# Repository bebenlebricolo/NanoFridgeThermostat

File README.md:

# NanoFridgeThermostat
Off-the-shelf fridge thermostat using an ArduinoNano to replace a broken fridge thermomechanical thermostat.

This project was born with the sole purpose of repairing a dying fridge whose thermostat was completely dead.
The idea is first to provide a very basic cooling support, with a simple on/off cycle that can be programmed using on seconds and off seconds.

The project also features a "bypass" switch that allows to manually trigger the fridge cooling process (useful for a fridge that first needs to be cooled down quite a lot before entering a "steady" on/off cycle ).

Polarity of said switch is meant for a circuit breaker switch type (because that's what I had around, so that explains why the logic is reversed.)
All components were components I had lying around :
* Arduino nano (clone, using the CH341 UART to USB bridge)
* Double relay board, with optoisolators as input.
* Wires and female header (single row, 2.54 mm pitch)
* Electrical tape to isolate components

# Future improvements
* Using a triac and triac driver as the main switching elements
    * Solid state is cool and removes the issue of relay contact points wearing down
* Adding a thermistor to measure temperature within the fridge and cycle towards a target temperature

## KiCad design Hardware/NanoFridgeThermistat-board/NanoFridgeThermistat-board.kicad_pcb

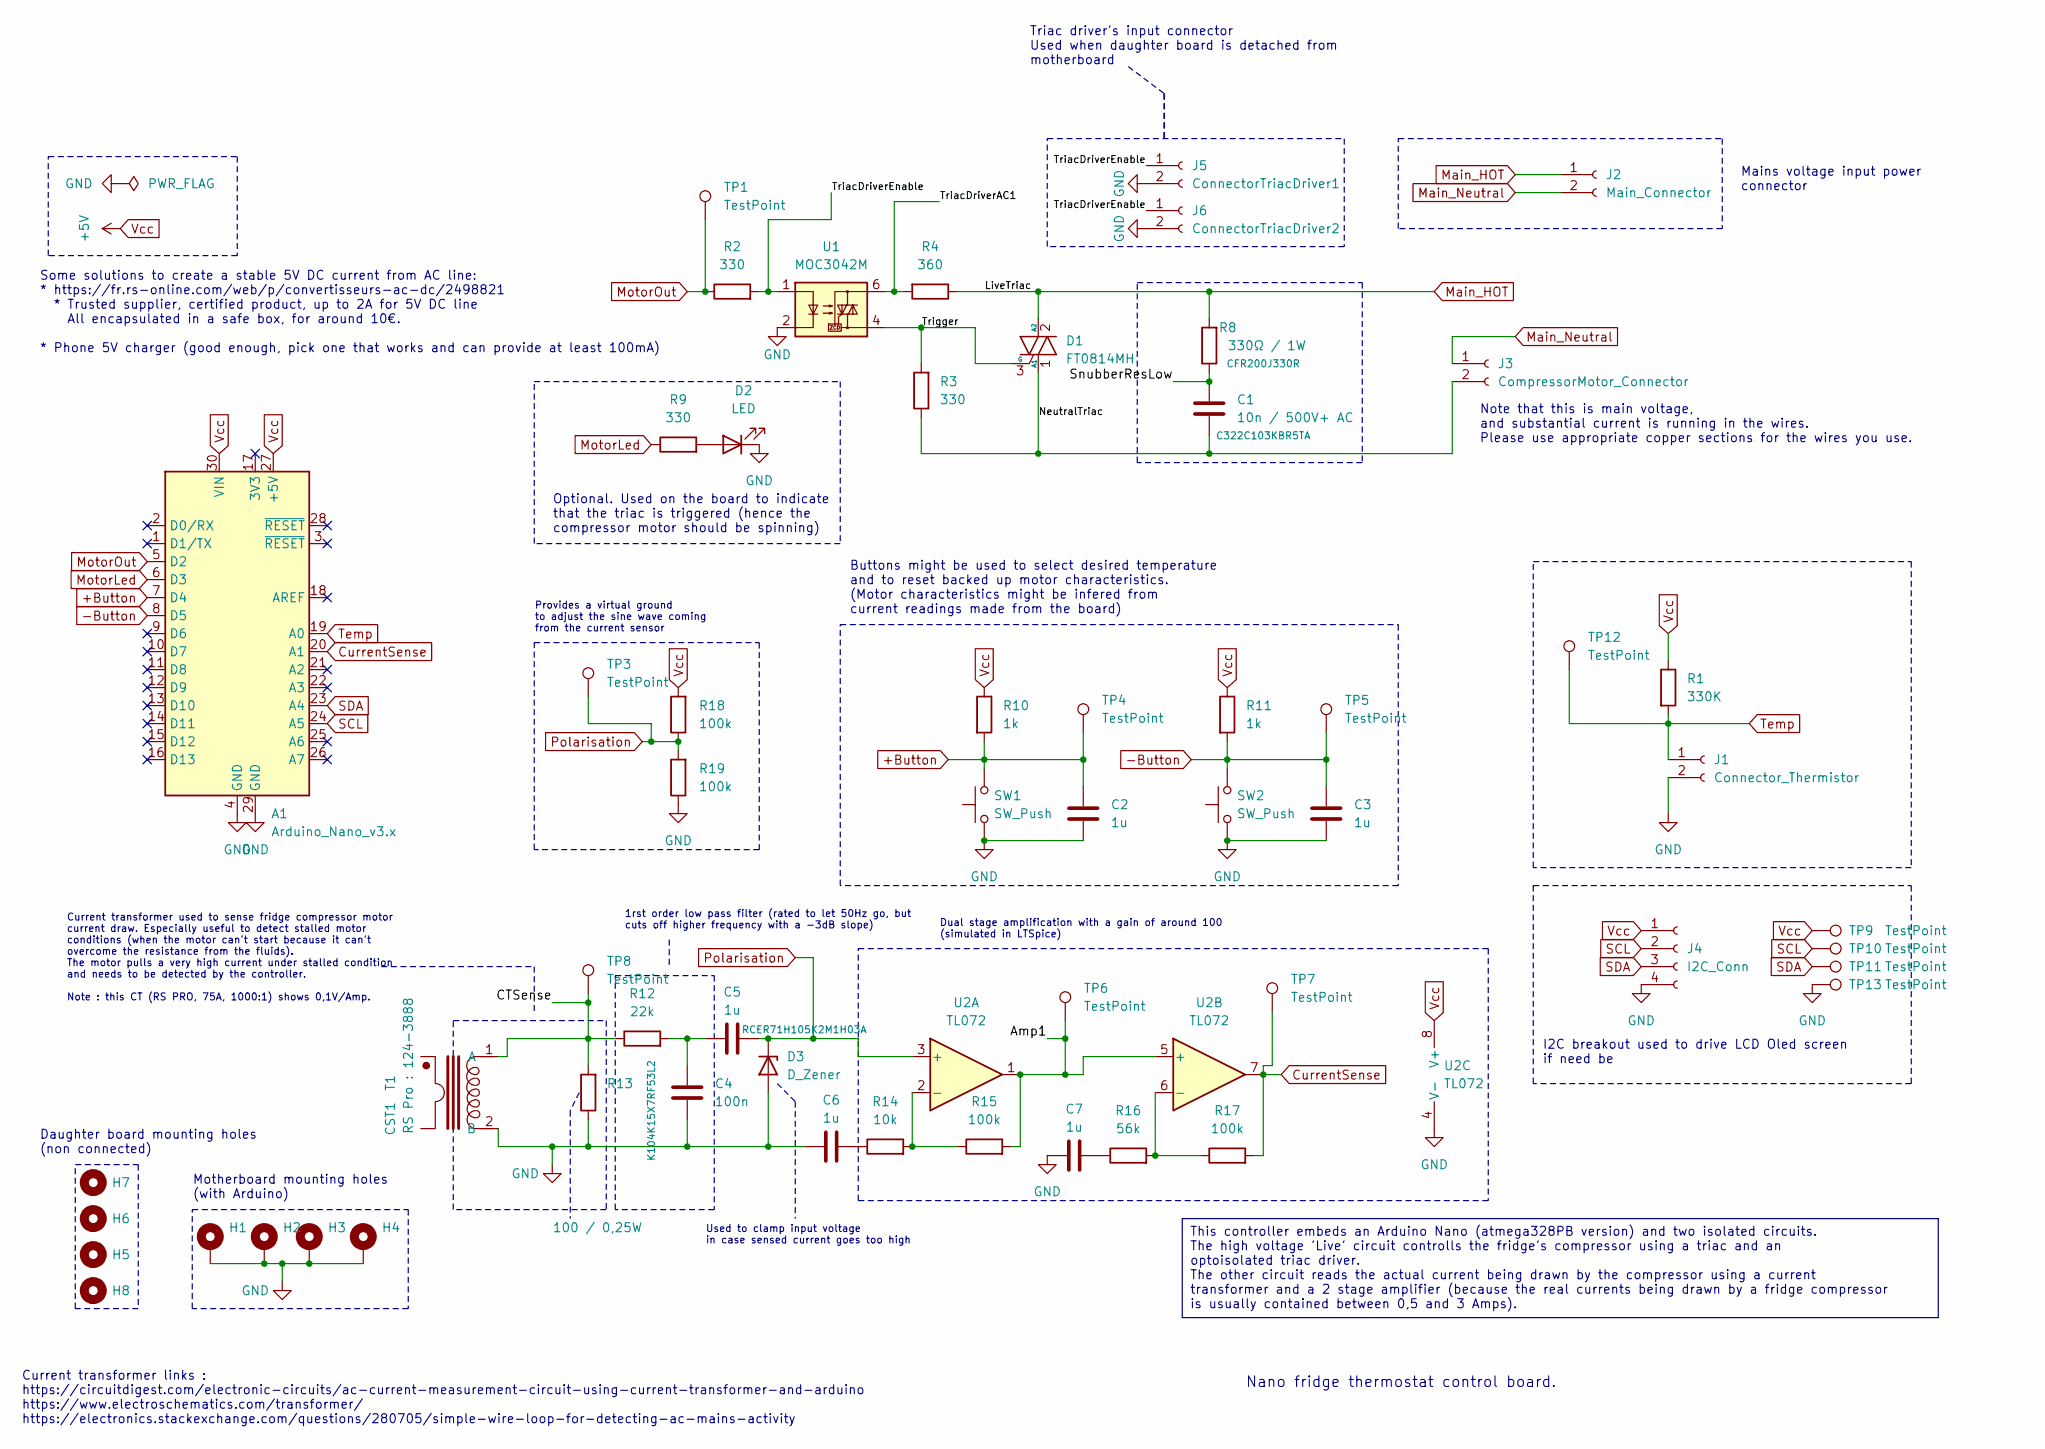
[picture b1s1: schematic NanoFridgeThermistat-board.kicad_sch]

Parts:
A1: Arduino_Nano_v3.x; Arduino_Nano
C1: 10n / 500V+ AC; C_Disc_D10.0mm_W2.5mm_P5.00mm
C2, C3, C5, C6, C7: 1u; C_Disc_D4.7mm_W2.5mm_P5.00mm
C4: 100n; C_Disc_D3.8mm_W2.6mm_P2.50mm
D1: FT0814MH; TO-220-3_Vertical
D2: LED; LED_D3.0mm
D3: D_Zener; D_DO-35_SOD27_P7.62mm_Horizontal
H1, H2, H3, H4: MountingHole_Pad; MountingHole_2.2mm_M2_DIN965_Pad
H5, H6, H7, H8: MountingHole; MountingHole_2.2mm_M2_ISO7380
J1: Connector_Thermistor; PinSocket_1x02_P2.54mm_Vertical
J2: Main_Connector; TE-282836-2-5.08mm
J3: CompressorMotor_Connector; TE-282836-2-5.08mm
J4: I2C_Conn; PinSocket_1x04_P2.54mm_Vertical
J5: ConnectorTriacDriver1; PinSocket_1x02_P2.54mm_Vertical
J6: ConnectorTriacDriver2; PinSocket_1x02_P2.54mm_Vertical
R1: 330K; R_Axial_DIN0207_L6.3mm_D2.5mm_P10.16mm_Horizontal
R2, R3, R9: 330; R_Axial_DIN0207_L6.3mm_D2.5mm_P10.16mm_Horizontal
R4: 360; R_Axial_DIN0207_L6.3mm_D2.5mm_P10.16mm_Horizontal
R8: 330Ω / 1W; R_Axial_DIN0614_L14.3mm_D5.7mm_P20.32mm_Horizontal
R10, R11: 1k; R_Axial_DIN0207_L6.3mm_D2.5mm_P10.16mm_Horizontal
R12: 22k; R_Axial_DIN0207_L6.3mm_D2.5mm_P10.16mm_Horizontal
R13: 100 / 0,25W; R_Axial_DIN0207_L6.3mm_D2.5mm_P10.16mm_Horizontal
R14: 10k; R_Axial_DIN0207_L6.3mm_D2.5mm_P10.16mm_Horizontal
R15, R17, R18, R19: 100k; R_Axial_DIN0207_L6.3mm_D2.5mm_P10.16mm_Horizontal
R16: 56k; R_Axial_DIN0207_L6.3mm_D2.5mm_P10.16mm_Horizontal
SW1, SW2: SW_Push; SW_PUSH_6mm
T1: CST1; CT-RSPRO-1243888
TP1, TP3, TP4, TP5, TP6, TP7, TP8, TP9, TP10, TP11, TP12, TP13: TestPoint; TestPoint_Pad_D1.0mm
U1: MOC3042M; DIP-6_W7.62mm
U2: TL072; DIP-8_W7.62mm

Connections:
+Button: A1.7 (D4), C2.1, R10.2, SW1.2, TP4.1
-Button: A1.8 (D5), C3.1, R11.2, SW2.2, TP5.1
/Amp1: R15.2, TP6.1, U2.1, U2.5 (+)
/CTSense: R12.1, R13.2, T1.1 (A), TP8.1
/NeutralTriac: C1.2, D1.1 (A1), J3.2, R3.1
/SnubberResLow: C1.1, R8.1
/TriacDriverAC1: R4.2, U1.6
/TriacDriverEnable: J5.1, J6.1, R2.2, U1.1
/Trigger: D1.3 (G), R3.2, U1.4
CurrentSense: A1.20 (A1), R17.2, TP7.1, U2.7
GND: A1.4 (GND), A1.29 (GND), C2.2, C3.2, C4.2, C6.1, C7.1, D2.1 (K), D3.2 (A), H1.1, H2.1, H3.1, H4.1, J1.2, J4.4, J5.2, J6.2, R13.1, R19.1, SW1.1, SW2.1, T1.2 (B), TP13.1, U1.2, U2.4 (V-)
Main_HOT: D1.2 (A2), J2.1, R4.1, R8.2
Main_Neutral: J2.2, J3.1
MotorLed: A1.6 (D3), R9.1
MotorOut: A1.5 (D2), R2.1, TP1.1
unnamed: C4.1, C5.1, R12.2
unnamed: C6.2, R14.1
unnamed: C7.2, R16.1
unnamed: D2.2 (A), R9.2
unnamed: R14.2, R15.1, U2.2 (-)
unnamed: R16.2, R17.1, U2.6 (-)
Polarisation: C5.2, D3.1 (K), R18.1, R19.2, TP3.1, U2.3 (+)
SCL: A1.24 (A5), J4.2, TP10.1
SDA: A1.23 (A4), J4.3, TP11.1
Temp: A1.19 (A0), J1.1, R1.2, TP12.1
Vcc: A1.27 (+5V), A1.30 (VIN), J4.1, R1.1, R10.1, R11.1, R18.2, TP9.1, U2.8 (V+)

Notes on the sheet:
This controller embeds an Arduino Nano (atmega328PB version) and two isolated circuits. The high voltage 'Live' circuit controlls the fridge's compressor using a triac and an optoisolated triac driver. The other circuit reads the actual current being drawn by the compressor using a current transfor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
Current transformer used to sense fridge compressor motor current draw. Especially useful to detect stalled motor conditions (when the motor can't start because it can't overcome the resistance from the fluids). The motor pulls a very high current under stalled condition and needs to be detected by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
Dual stage amplification with a gain of around 100 (simulated in LTSpice)
Triac driver's input connector Used when daughter board is detached from motherboard
Note that this is main voltage, and substantial current is running in the wires. Please use appropriate copper sections for the wires you use.
Provides a virtual ground to adjust the sine wave coming from the current sensor
Nano fridge thermostat control board.
1rst order low pass filter (rated to let 50Hz go, but cuts off higher frequency with a -3dB slope)
Daughter board mounting holes (non connected)
Optional. Used on the board to indicate that the triac is triggered (hence the compressor motor should be spinning)
Some solutions to create a stable 5V DC current from AC line: * https://fr.rs-online.com/web/p/convertisseurs-ac-dc/2498821 * Trusted supplier, certified product, up to 2A for 5V DC line All encapsulated in a safe box, for around 10€. * Phone 5V charger (good enough, pick one that works and can pro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
Buttons might be used to select desired temperature and to reset backed up motor characteristics. (Motor characteristics might be infered from current readings made from the board)
Motherboard mounting holes (with Arduino)
Mains voltage input power connector
I2C breakout used to drive LCD Oled screen if need be
Used to clamp input voltage in case sensed current goes too high
Current transformer links : https://circuitdigest.com/electronic-circuits/ac-current-measurement-circuit-using-current-transformer-and-arduino https://www.electroschematics.com/transformer/ https://electronics.stackexchange.com/questions/280705/simple-wire-loop-for-detecting-ac-mains-activity

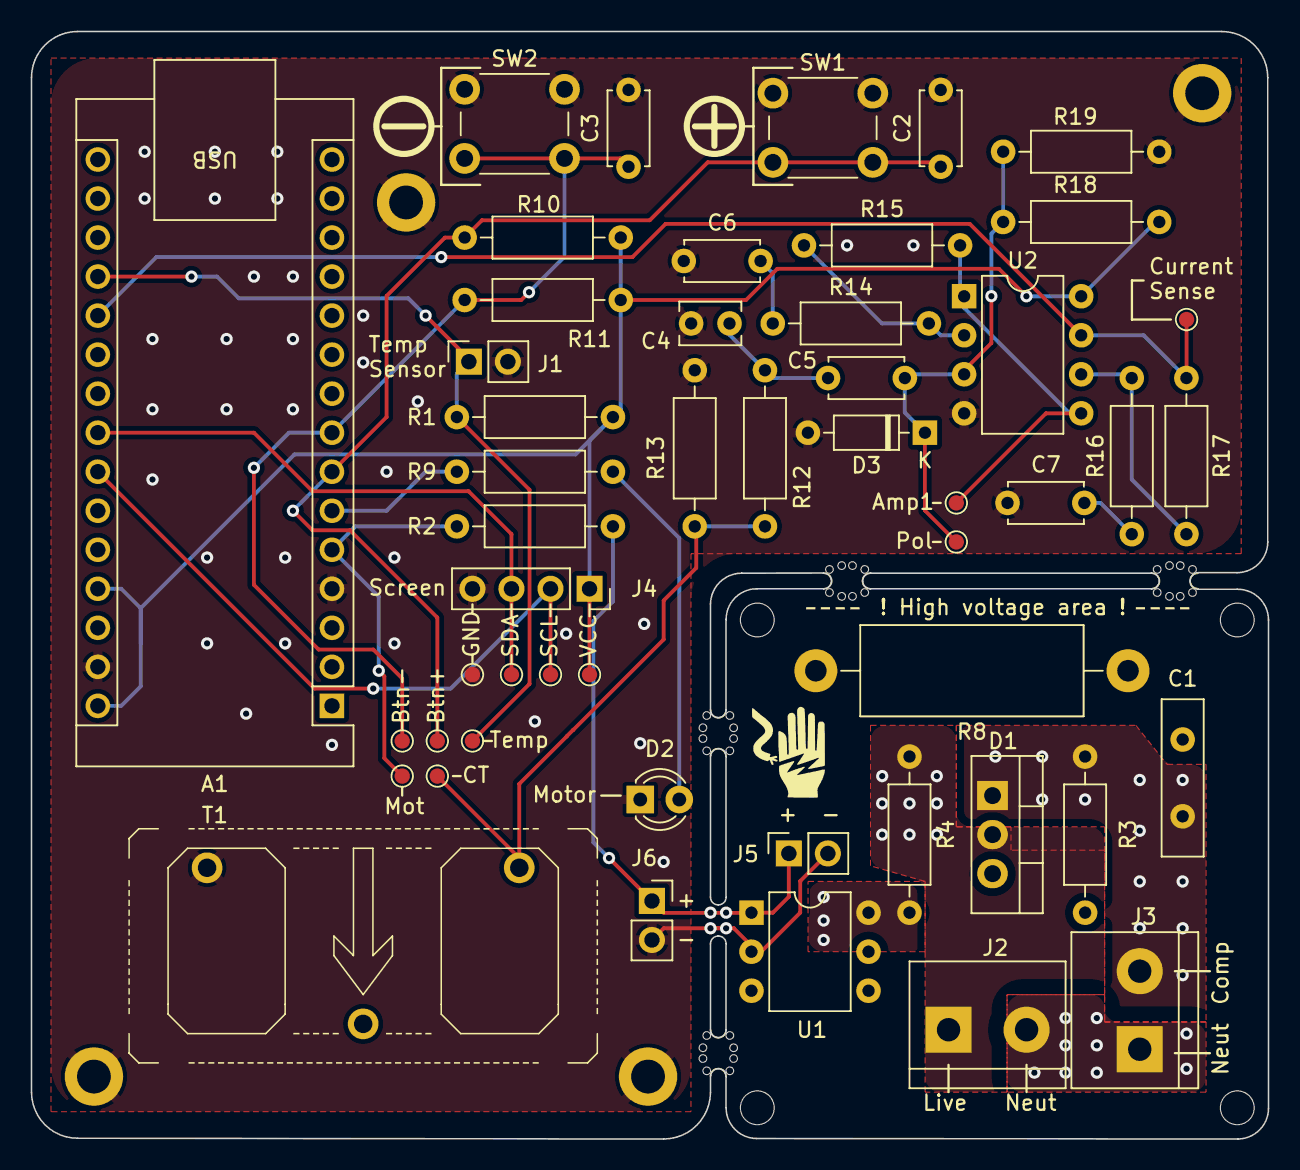
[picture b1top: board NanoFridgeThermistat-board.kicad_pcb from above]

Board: 2 copper layers, 80.5 x 72.1 mm, 62 parts (0 on the bottom side), 26 nets.

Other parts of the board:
mouse-bite-1mm-slot, mouse-bite-1mm-slot#2, mouse-bite-1mm-slot#3, mouse-bite-1mm-slot#4: VAL**; mouse-bite-1mm-slot

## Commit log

2023-11-28 Added simple arduino project, using very basic timer features
2023-11-28 Added a bit of stuff in the Readme
2023-12-15 Moved sketch so that it pleases Arduino Ide
2023-12-15 Added NTC calculus & characterization spreadsheet
2023-12-15 reworked file and folder structure to split from version 1 to version 2
2024-01-22 Added prototype for thermistors source files
2024-01-22 Added python source file generator for thermistors
2024-01-23 Added resistor bridge calculator script
2024-01-23 Improved doc
2024-01-23 Moved tools in Tools/ folder
2024-01-24 Tweaked generators and implemented interpolators
2024-01-24 Added CMake support to test the project
2024-01-25 Fixing thermistor_generator data count
2024-01-25 Trying to get this working with Windows
2024-01-25 Fixing for linux as well
2024-01-26 Improved CMake infrastructure
2024-01-26 Implemented uint16_t to int8_t interpolation
2024-01-26 Implemented and tested thermistor code
2024-01-26 Improved thermistor generator
2024-01-26 Improved data generation with proper integer rounding
2024-01-26 Updated documentation
2024-01-28 Added hardware layout with board
2024-01-28 Improved routing for hardware
2024-01-29 Added resistor bridge sources
2024-01-30 Added one more bridge resistor test
2024-01-31 Removed fp-info-cache from the codebase
2024-02-06 Added platformio to ease Arduino developments with real project structure
2024-02-06 Added AC current sensing sim file with LTSpice (dual stage op amp)
2024-02-06 Finalized board with testing points and mouse bites to detach AC board
2024-02-06 Adding mounting holes and test points
2024-02-06 Added CERN_OHL_V2 S license to hardware
2024-02-06 Fixed last issues with DRC on PCB router
2024-02-06 Changed base color of the board
2024-02-06 Removed unused components
2024-02-06 Added current sense hardware layout
2024-02-06 Added current transformers selection spreadsheet
2024-02-06 Added buttons and starting current sensor addition
2024-02-06 Upgraded board with new models, components and layout
2024-02-06 Updated spreadsheets
2024-02-06 Added mother-daughter boards connector on mother board as well
2024-02-06 Stabilized Gtest support on Windows and Linux
2024-02-06 Added more parts sourcing
2024-02-07 moved Panelization footprint and tidied Spreadsheets
2024-02-07 Generated Gerbers files
2024-02-07 Added drill files
2024-02-07 Added Open Source Hardware logo to boards
2024-02-07 Updated documentation, added screenshots
2024-02-07 Exported board assembly as 3D step files
2024-02-09 Removed V1 and renamed codebase to Firmware folder
2024-02-09 Added basic functionalities guidelines
2024-02-11 Added persistent memory
2024-02-11 Wiring things up
2024-02-14 Improved a bit clang format and reformated a bit the codebase
2024-02-14 Reworked timebase to also count milliseconds (to allow 500-1Kz operations)
2024-02-14 Added throttled analog reads, sensors are not read at every turn of the loop
2024-02-15 Used button events to change temperature set point
2024-02-16 Added timebase time processing
2024-02-19 Adding basic temperature control + reformats
2024-02-21 Splitted source files into Core and Hal libraries
2024-02-22 Added current module test -> RMS calculation
2024-02-22 Improved a little bit current module with arbitrary RMS calculation
2024-02-23 WIP : LED driver + time refactor
2024-02-23 Tweaking clang-formatc tools
2024-02-23 Updated clang format
2024-02-23 Added uint8_t interpolation
2024-02-23 WIP Led implementation
2024-02-26 Updated clang-format config
2024-02-26 Refactored a bit led config and implemented led on/off in breathing mode
2024-02-27 Added led_tests
2024-02-27 WIP adding accept pattern implementation
2024-02-27 Implemented and tested led accept pattern
2024-02-28 Added duty sawtooth helper tests
2024-02-28 Fixed interpolation overflowing issues
2024-02-28 WIP trying to test the breathing pattern
2024-03-06 First upload to the board with blinking LED
2024-03-07 WIP Working on breathing mode
2024-03-08 Added Serial prints (optional) and fixed Bridge implem (data overflows)
2024-03-08 Added a Spanner (distribution) algorithm to spread data evenly in a sequence
    * Spanner algorithm distributes data evenly in a given data sequence
    * Useful to implement LED Pulse density modulation when frequency is
    around 100 Hz
    * Will be used to dim the LED smoothly (virtual resolution of 100 steps,
    10ms actuation max)
2024-03-08 Improved LED system, pulse stuffing is not adapted for this purpose. Higher frequency is.
2024-03-08 harware : swapped misplaced buttons
2024-03-08 Improved ON time of the LED by centering values lower
2024-03-13 Implemented lots of debug serial and fixed all functional aspects
2024-03-13 Trying to have a good current reading
2024-03-13 Fixed Header and Footer EEPROM reads
2024-03-15 Added time guards before running the motor after a stop
    * Changed motor cycling conditions to avoid running in Stalled condition
    when we don't wait enough time
    * This happens if the temperature sensor sees fast temperature
    variations oscillating in and out the hysteresis window.
    * Prevents the motor to start if it was shut down less than 5 minutes
    ago
2024-03-15 Improved motor start wait period when we've just booted
2024-03-20 Repaired broken build
2024-04-17 Updated codebase toward better current sensing
2024-04-17 Updated KiCad project files
2024-04-19 Improved current measurements and fixed timing issues ; now RMS is good
2024-04-19 Enabled an immune period after stalled motor condition to allow the motor to get back up to speed
2024-04-19 Added measured currents spreadsheet
2024-04-19 Added capability to set the LED state when falling back to NONE pattern
2024-04-26 Added NO_CURRENT_MONITORING control define which removes the need for a current detector
2024-05-06 Did some cleanup
2024-05-06 Added test animations with pixelorama and krita
2024-05-08 Added icons and images exports
2024-05-08 Added Wokwi UI Test project
2024-05-16 Added compressor animation
2024-05-29 Added numbers small and started implementing little font renderer
2024-06-05 WIP added custom itoa implement to split digits
2024-06-10 WIP : Transfered number_small for testing
2024-06-28 Reorganized source code
2024-06-28 Added some simple data filtering tools
2024-07-03 WIP working on numbers printing
2024-07-03 Improved numbers drawing algorithm + bitmap struct

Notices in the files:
Hardware/NanoFridgeThermistat-board/NanoFridgeThermistat-board.kicad_pcb:
Licensed under CERN OHL V2
